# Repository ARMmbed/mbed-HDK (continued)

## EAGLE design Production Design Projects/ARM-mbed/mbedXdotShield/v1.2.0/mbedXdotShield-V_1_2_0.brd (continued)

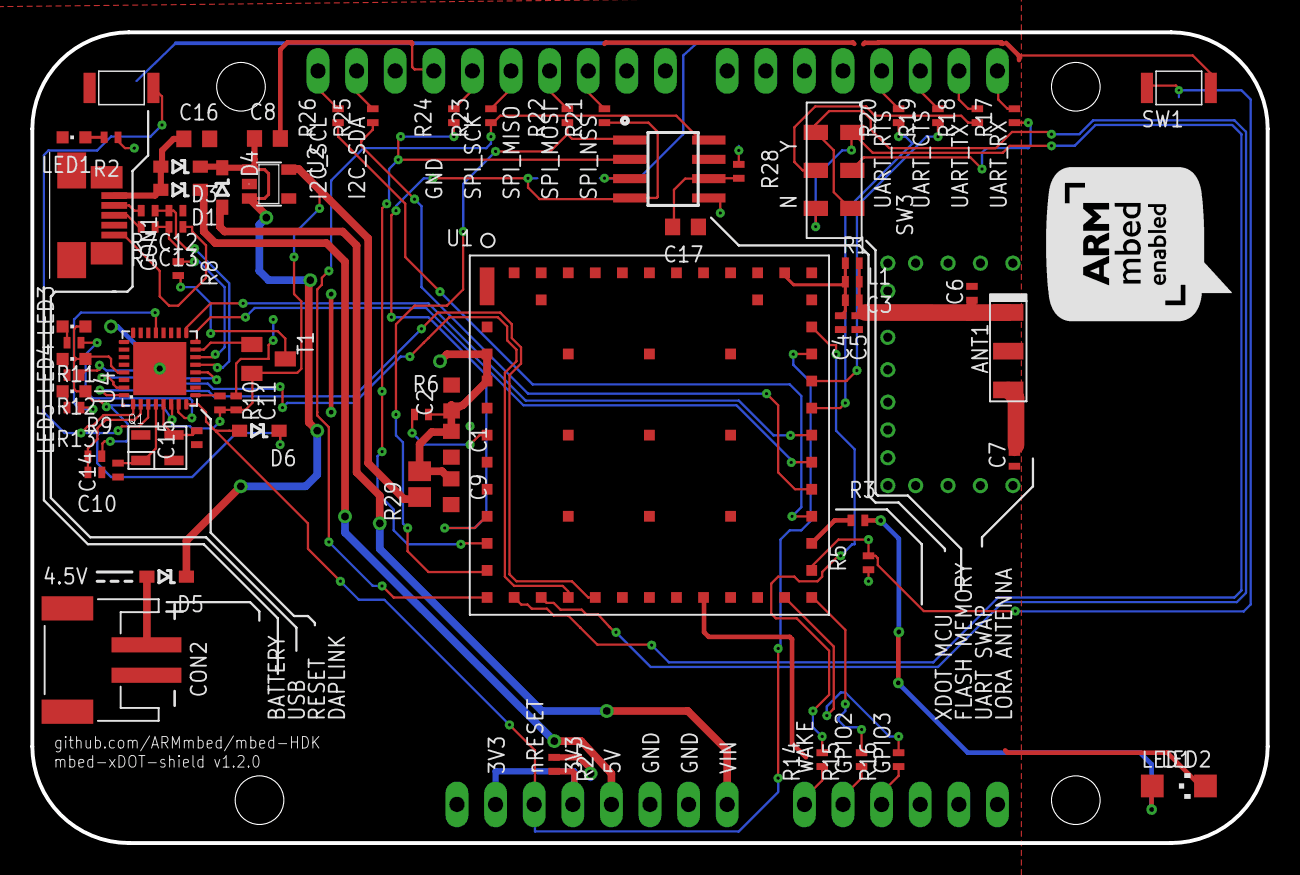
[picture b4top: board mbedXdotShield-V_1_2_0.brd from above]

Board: 2 copper layers, 81.3 x 53.3 mm, 70 parts (0 on the bottom side), 68 nets.

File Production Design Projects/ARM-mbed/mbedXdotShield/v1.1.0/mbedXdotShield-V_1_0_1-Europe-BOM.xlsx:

Qty | Value | Device | Package | Parts | Description | MF | MFN | OC-DIGIKEY | OC-MOUSER | OC-NEWARK
1 |  | IF-LPC11U35 | HVQFN33 | U4 | MCU | NXP | LPC11U35FHI33/501, | 568-9586-ND | 771-LPC11U35FHI33501 | 24W5342
3 | 0 | RESISTOR0402 | 402 | R6, R27, R28 | Resistor | Yageo | RC0402JR-070RL | 311-0.0JRCT-ND | 603-RC0402JR-070RL | 603-RC0402JR-070RL
5 | 1.5K | RESISTOR0402 | 402 | R2, R5, R8, R12, R13 | Resistor | Panasonic | ERJ-2RKF1501X | P1.50KLCT-ND | 667-ERJ-2RKF1501X | 2302656
3 | 100nF | CAPACITOR0402 | 402 | C10, C11 | Capacitor | AVX | 0402YD104KAT2A | 478-1126-1-ND | 581-0402YD104K | 1327666
3 | 100nF | CAPACITOR0603 | 603 | C2, C17 | Capacitor | AVX | 0603YC104KAT2A | 478-1239-1-ND | 581-060316C104K | 1327679
3 | 10K | RESISTOR0402 | 402 | R9, R10 | Resistor | Vishay | CRCW040210K0JNED | 541-10KJCT-ND | 71-CRCW0402J-10K-E3 | 59M6696
3 | 10uF | CAPACITOR0603 | 603 | C1, C8, C9, C16 | Capacitor | Yageo | CC0603MRX5R5BB106 | 311-1448-1-ND | 603-CC603MRX5R5BB106 | 1458902
3 | 12MHz | Q_3.2X2.5 | 3.2X.2.5 | Q1 | XTAL | TXC | 7M-12.000MAAJ-T | 887-1121-1-ND | 717-7M-12.000MAAJ-T | 84R5706
3 | 18pF | CAPACITOR0402 | 402 | C12, C13, C14, C15 | Capacitor | Murata | GRM1555C1H180JA01D | 490-5858-6-ND |  | 14T3293
14 | 220R | RESISTOR0402 | 402 | R3, R14, R15, R16, R17, R18, R19, R20, R21, R22, R23, R24, R25, R26 | Resistor | Vishay | CRCW0402220RJNED | 541-220JCT-ND | 71-CRCW0402J-220-E3 | 1514687
3 | 33R | RESISTOR0402 | 402 | R4, R7 | Resistor | Vishay | CRCW040233R0JNED | 541-33JCT-ND | 71-CRCW0402J-33-E3 | 72M6782
1 | 470R | RESISTOR0402 | 402 | R11 | Resistor | Vishay | CRCW0402470RJNED | 541-470JCT-ND | 71-CRCW0402J-470-E3 | 59M6737
3 | 47346-0001 | 47346-0001 | USB-MICRO-B-H | CON1 | USB Receptacle Horizontal Micro Type B | MOLEX | 47346-0001 |  | 538-47346-0001 | 1568026
3 | 5.6pF | CAPACITOR0402 | 402 | C4 | Capacitor | AVX | 04025U5R6BAT2A | 478-10162-1-ND | 581-04025U5R6BAT2A | 1327642RL
3 | 6.8pF | CAPACITOR0402 | 402 | C7 | Capacitor | Murata | GRM1555C1H6R8BA01D | 490-6252-1-ND | 81-GRM1555C1H6R8BA1D | 2611902
3 | 82pF | CAPACITOR0402 | 402 | C6 | Capacitor | Murata | GRM1555C1H820JA01D | 490-5879-1-ND | 81-GRM1555C1H820JA1D | 2470460
3 | 9.1pF | CAPACITOR0402 | 402 | C3 | Capacitor | Murata | GJM1555C1H9R1CB01D | 490-3112-1-ND | 81-GJM1555C1H9R1CB01 | 41M1583
3 | AT45DB321E-SHF-B | AT45DB321E-SHF-B | SO8 | U3 | Serial Flash 32 Mb 85 Mhz | Adesto Technologies | AT45DB321E-SHF-B | 1265-1072-5-ND | 988-AT45DB321E-SHF-B | 2414318
3 | BAT60A | BAT60A | SOD323 | D1, D2, D3, D4, D5 | SCHOTTKY DIODE | Infineon | BAT60AE6327HTSA1 | BAT60AE6327HTSA1CT-ND | 726-BAT60AE6327 | 85X4127
3 | BAT60J | BAT60J | SOD323 | D6 | SCHOTTKY DIODE | STMicroelectronics | BAT60JFILM | 497-3707-6-ND | 511-BAT60JFILM | 89K1218
3 | BLUE | SMD_LED0603 | CHIPLED_0603 | LED4 | LED SMD, Colour Blue | Wurth Electronics Inc | 150060BS75000 | 732-4966-1-ND | 710-150060BS75000 | 2322069
3 | BSS84 | BSS84 | SOT23-3 | T1 | MOSFET P-CHANNEL | Fairchild Semiconductor | BSS84 | BSS84CT-ND | 512-BSS84 | 58K8770
3 | GREEN | SMD_LED0603 | CHIPLED_0603 | LED5 | LED SMD, Colour Green | Wurth Electronics Inc | 150060GS75000 | 732-4971-1-ND | 710-150060GS75000 | 2322070
3 | K64F/K22F-SHIELD | K64F/K22F-SHIELD | K64F/K22F | BRD1 | Shield for K64F/K22F | SparkFun | 1568-1413-ND
3 | M620720 | M620720 | M620720 | ANT1 | Chip Antenna Ceramic ISM/M2M/IoT 868/915MHz | Ethertronics | M620720 | 939-1066-1-ND
3 | MTXDOT-EU1-A00-1 | MTXDOT-EU1-A00-1 | MTXDOT-EU1/NA1-A00-1 | U1 | Multitech xDOT LORA MODULE UFL/TRC 868MHz for Europe | Multi-Tech Systems Inc. | MTXDOT-EU1-A00-1 | 591-1292-ND
3 | RED | SMD_LED0603 | CHIPLED_0603 | LED1, LED3 | LED SMD, Colour Red | Wurth Electronics Inc | 150060RS75000 | 732-4978-1-ND | 710-150060RS75000 | 2322071
3 | S2B-PH-SM4-TB(LF)(SN) | S2B-PH-SM4-TB(LF)(SN) | S2B-PH-SM4-TB(LF)(SN) | CON2 | 2 Position 2 mm JST PH Series Pitch Surface Mount Side Entry Shrouded Header | JST | S2B-PH-SM4-TB(LF)(SN) | 455-1749-1-ND |  | 38K8067
3 | SKRKAEE010 | SKRKAEE010 | SKRKAEE010 | RESET, SW2 | MOMENTARY SWITCH PUSH VERTICAL (SPST) | ALPS | SKRKAEE010 |  | 688-SKRKAE
3 | SMD_LED1206 | SMD_LED1206 | CHIPLED_1206 | LED2 | LED SMD, Colour Blue | Wurth Electronics Inc | 150120BS75000 | 732-4989-1-ND | 710-150120BS75000 | 2322084
3 | TLV73333PDBVT | TLV73333PDBVT | SOT23-5 | U2 | LDO Fixed Regulator 3.3v, 300mA | Texas Instruments | TLV73333PDBVT | 296-38492-1-ND | 595-TLV73333PDBVT | 2455145
3 | JS202011JCQN | JS202011JCQN | JS202011JCQN | SW3 | SLIDE TOGGLE SWITCH VERTICAL (DPDT) | C&K Components | JS202011JCQN | CKN10723CT-ND | 611-JS202011JCQN

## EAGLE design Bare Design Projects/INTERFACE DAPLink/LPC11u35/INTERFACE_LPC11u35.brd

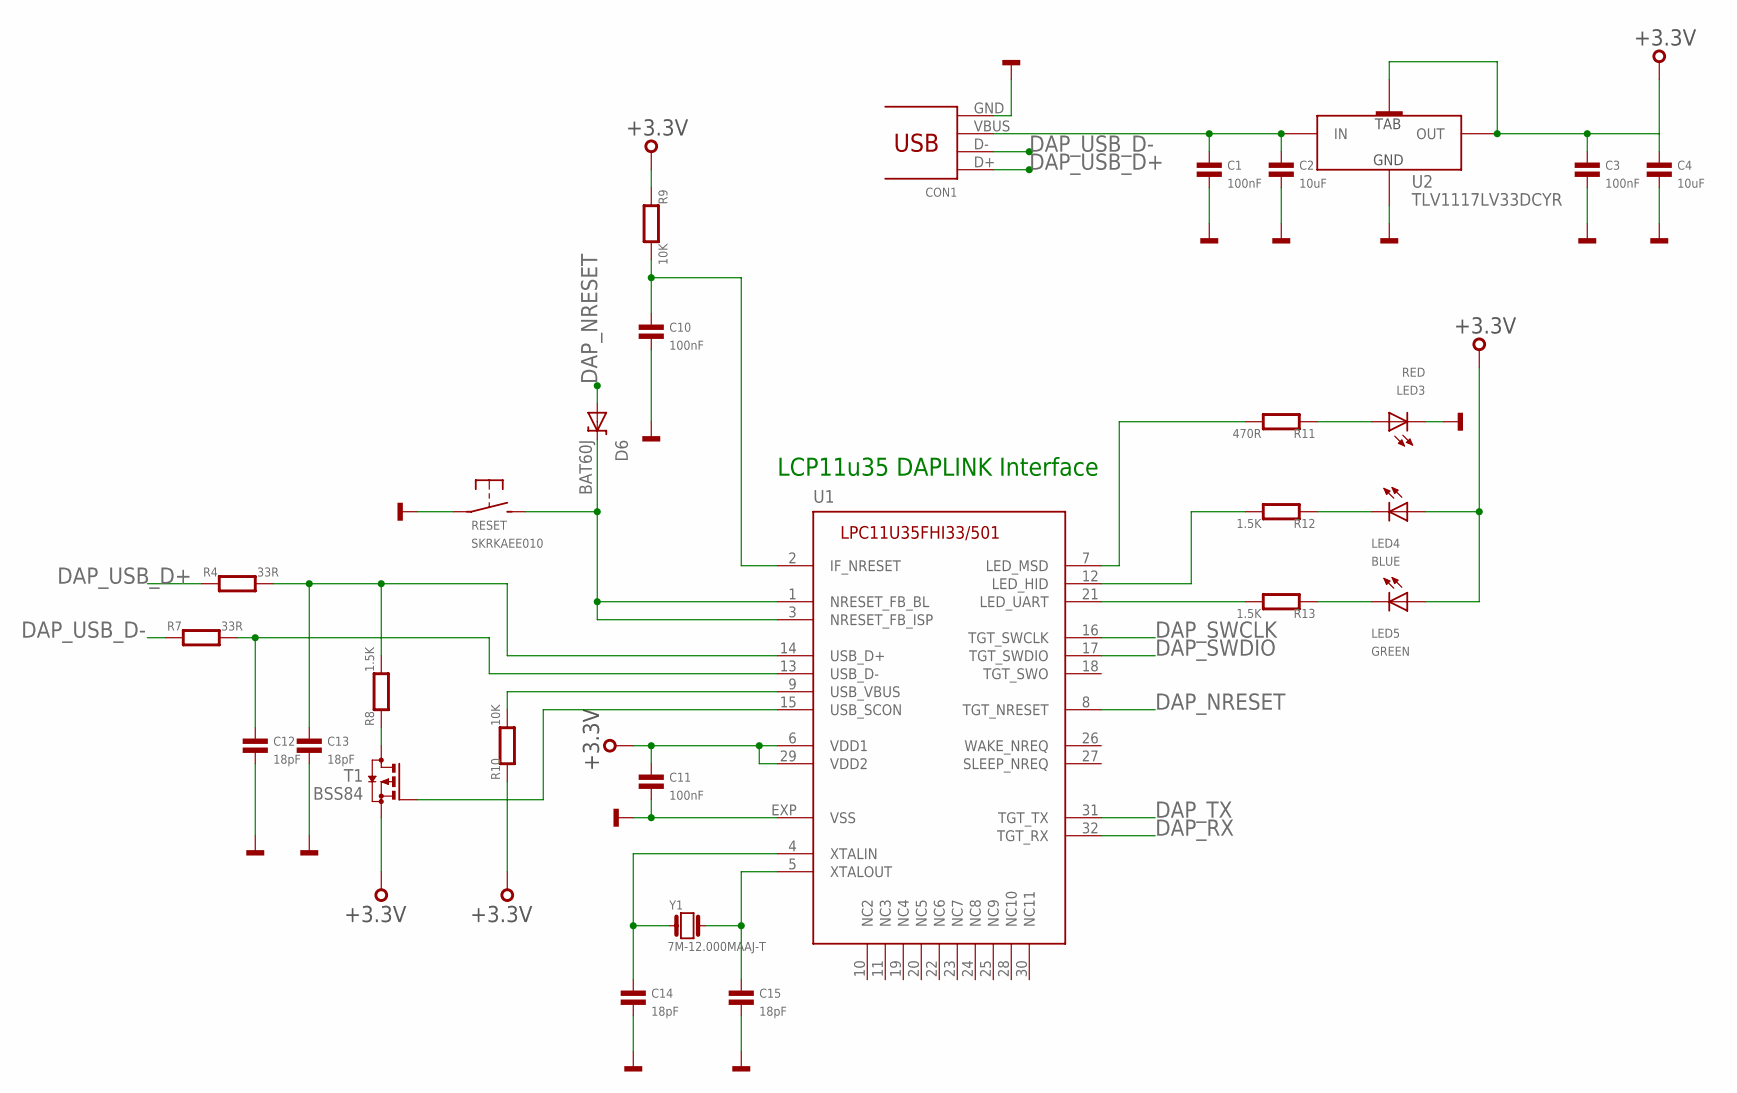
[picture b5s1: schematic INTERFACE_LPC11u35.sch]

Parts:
C1, C3, C10, C11: 100nF; 0402
C2, C4: 10uF; 0603
C12, C13, C14, C15: 18pF; 0402
CON1: 47346-0001; USB-MICRO-B-H
D6: BAT60J; SOD323
LED3: RED; CHIPLED_0603
LED4: BLUE; CHIPLED_0603
LED5: GREEN; CHIPLED_0603
R4, R7: 33R; 0402
R8, R12, R13: 1.5K; 0402
R9, R10: 10K; 0402
R11: 470R; 0402
RESET: SKRKAEE010
T1: BSS84; SOT23-3
U1: IF_LPC11U35FHI33/501; HVQFN33
U2: TLV1117LV33DCYR; SOT223
Y1: 7M-12.000MAAJ-T; 3.2X.2.5

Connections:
+3.3V: C3.1, C4.1, C11.1, LED4.A, LED5.A, R9.1, R10.1, T1.2 (S), U1.6 (VDD1), U1.29 (VDD2), U2.OUT(1) (OUT), U2.OUT(2) (TAB)
DAP_NRESET: D6.A, U1.8 (TGT_NRESET)
DAP_RX: U1.32 (TGT_RX)
DAP_SWCLK: U1.16 (TGT_SWCLK)
DAP_SWDIO: U1.17 (TGT_SWDIO)
DAP_TX: U1.31 (TGT_TX)
DAP_USB_D+: CON1.D+, R4.1
DAP_USB_D-: CON1.D-, R7.1
GND: C1.2, C2.2, C3.2, C4.2, C10.2, C11.2, C12.2, C13.2, C14.2, C15.2, CON1.GND, LED3.C, RESET.P$1, U1.EXP (VSS), U2.GND
HID: R12.2, U1.12 (LED_HID)
IF_NRESET: C10.1, R9.2, U1.2 (IF_NRESET)
ISP: D6.K, RESET.P$2 (S), U1.1 (NRESET_FB_BL), U1.3 (NRESET_FB_ISP)
MSD: R11.2, U1.7 (LED_MSD)
unnamed: C1.1, C2.1, CON1.VBUS, U2.IN
unnamed: LED3.A, R11.1
unnamed: C13.1, R4.2, R8.2, U1.14 (USB_D+)
unnamed: C12.1, R7.2, U1.13 (USB_D-)
unnamed: T1.1 (G), U1.15 (USB_SCON)
unnamed: R8.1, T1.3 (D)
unnamed: R10.2, U1.9 (USB_VBUS)
unnamed: LED4.C, R12.1
unnamed: LED5.C, R13.1
unnamed: C15.1, U1.5 (XTALOUT), Y1.P$3 (2)
unnamed: C14.1, U1.4 (XTALIN), Y1.P$1 (1)
UART: R13.2, U1.21 (LED_UART)

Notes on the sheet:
LCP11u35 DAPLINK Interface

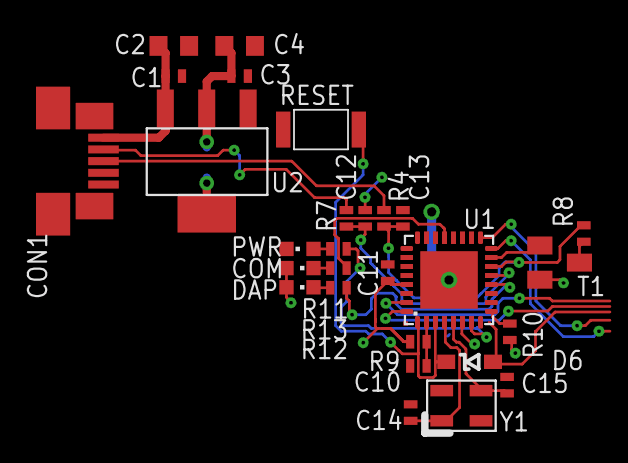
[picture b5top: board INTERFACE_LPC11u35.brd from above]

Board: 2 copper layers, 28 parts (0 on the bottom side), 21 nets.

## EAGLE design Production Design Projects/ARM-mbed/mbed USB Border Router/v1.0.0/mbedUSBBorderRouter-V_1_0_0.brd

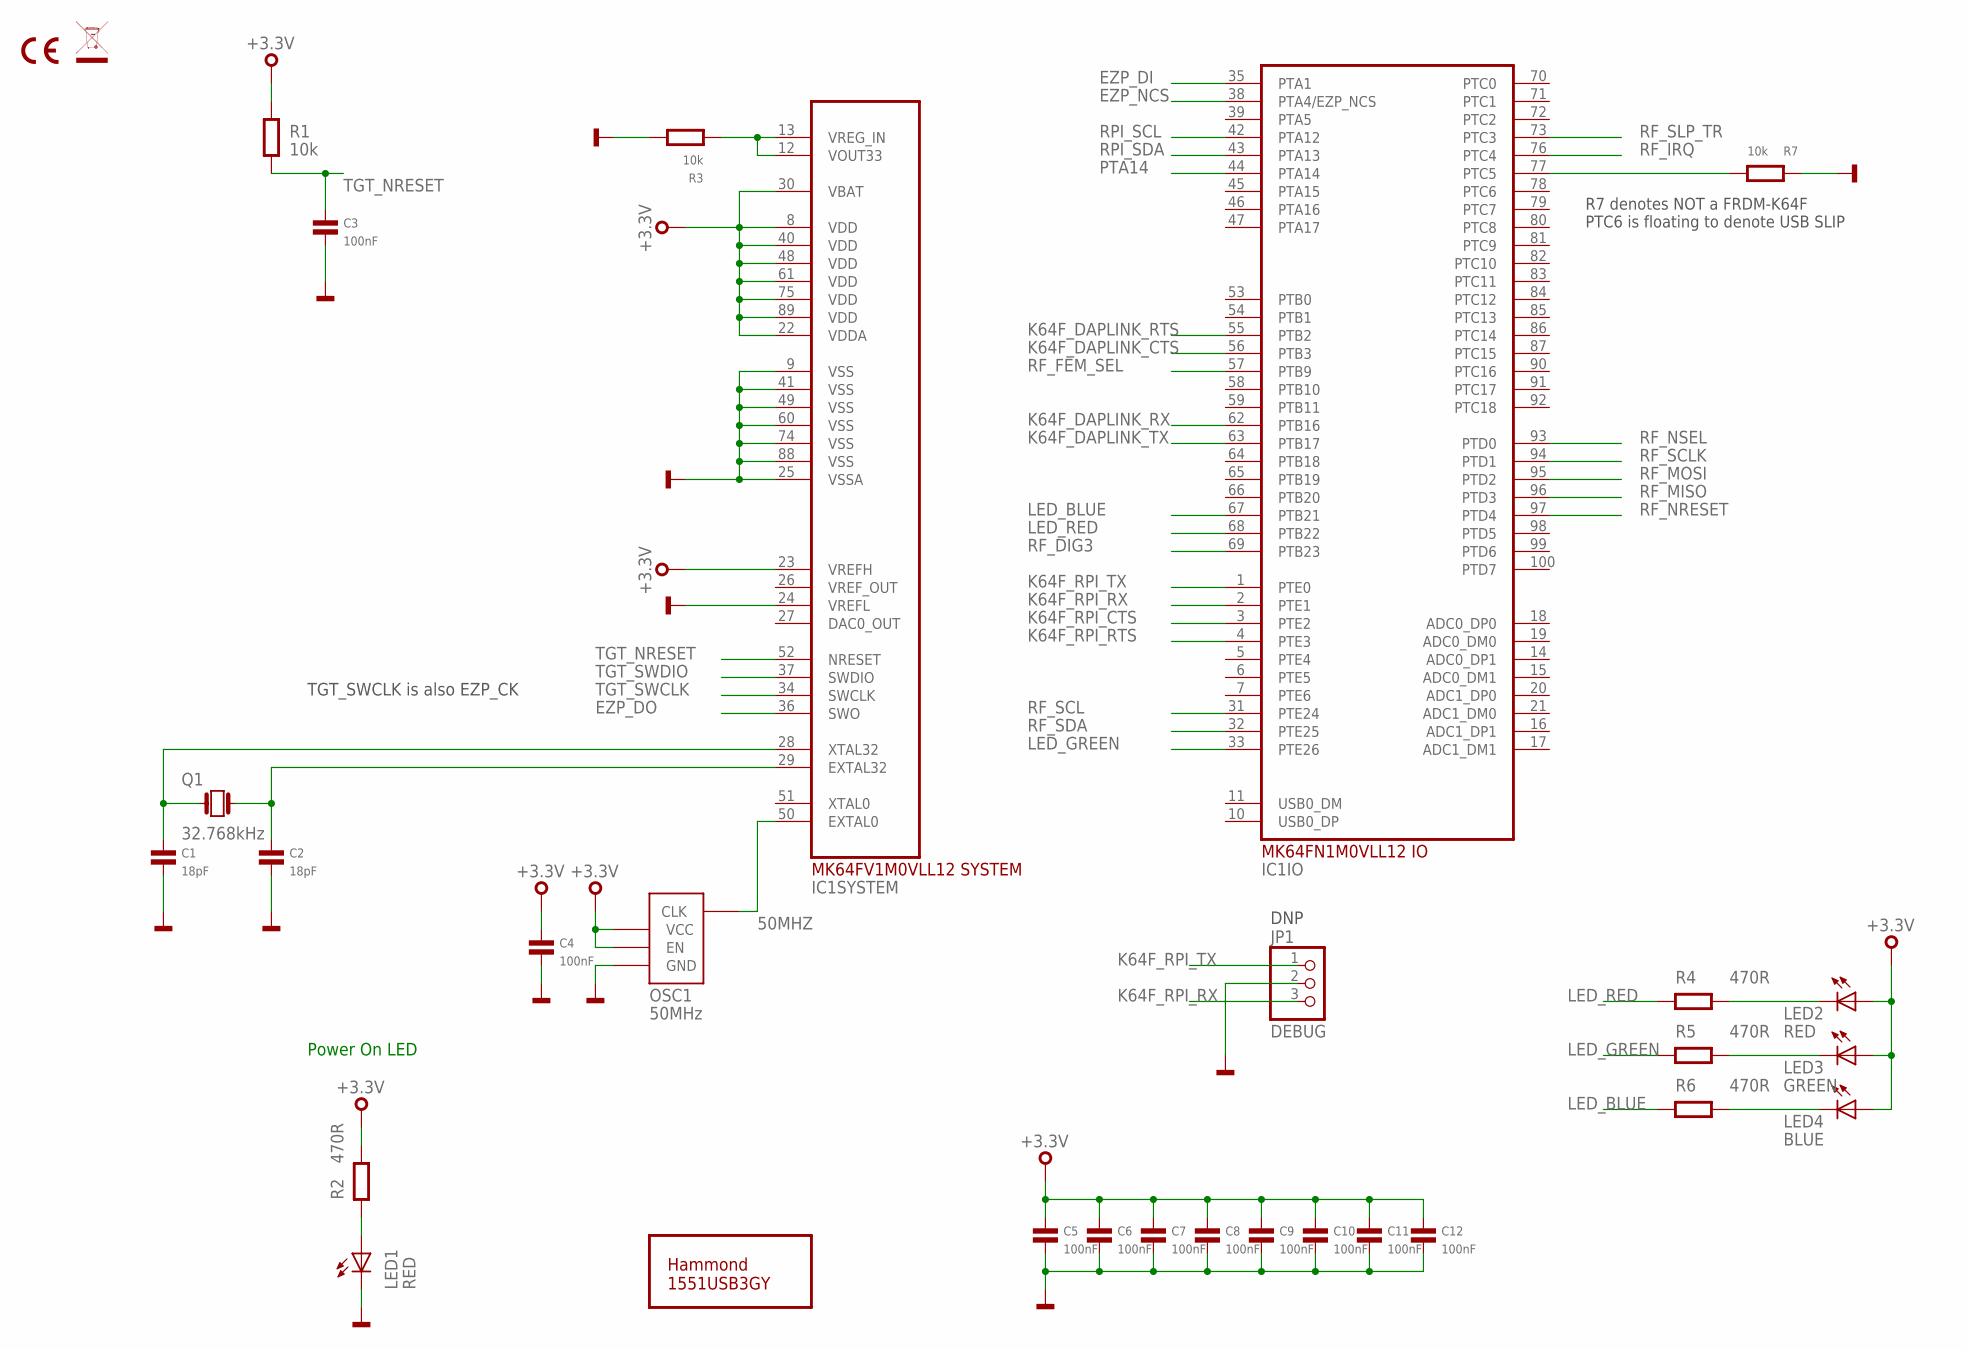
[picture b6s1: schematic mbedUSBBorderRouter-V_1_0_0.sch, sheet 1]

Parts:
BRD1: HAMMOND-1551USB3GY
C1, C2: 18pF; 0402
C3, C4, C5, C6, C7, C8, C9, C10, C11, C12: 100nF; 0402
IC1: MK64FN1M0VLL12; LQFP100
JP1: DEBUG; 1X03
LED1, LED2: RED; CHIPLED_0603
LED3: GREEN; CHIPLED_0603
LED4: BLUE; CHIPLED_0603
OSC1: 50MHz; 3.2X.2.5
Q1: 32.768kHz; FC135
R1, R3, R7: 10k; 0402
R2, R4, R5, R6: 470R; 0402
SS1: CE-MARK; CE-MARK-0.2
SS2: WEEE-MARK; WEEE-MARK-0.2

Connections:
50MHZ: IC1.50 (EXTAL0), OSC1.P$3 (CLK)
+3.3V: C4.1, C5.1, C6.1, C7.1, C8.1, C9.1, C10.1, C11.1, C12.1, IC1.8 (VDD), IC1.22 (VDDA), IC1.23 (VREFH), IC1.30 (VBAT), IC1.40 (VDD), IC1.48 (VDD), IC1.61 (VDD), IC1.75 (VDD), IC1.89 (VDD), LED2.A, LED3.A, LED4.A, OSC1.P$1 (EN), OSC1.P$4 (VCC), R1.2, R2.2; also elsewhere on the board
EZP_DI: IC1.35 (PTA1)
EZP_DO: IC1.36 (SWO)
EZP_NCS: IC1.38 (PTA4/EZP_NCS)
GND: C1.2, C2.2, C3.2, C4.2, C5.2, C6.2, C7.2, C8.2, C9.2, C10.2, C11.2, C12.2, IC1.9 (VSS), IC1.24 (VREFL), IC1.25 (VSSA), IC1.41 (VSS), IC1.49 (VSS), IC1.60 (VSS), IC1.74 (VSS), IC1.88 (VSS), JP1.2, LED1.C, OSC1.P$2 (GND), R3.2, R7.2; also elsewhere on the board
K64F_DAPLINK_CTS: IC1.56 (PTB3); also elsewhere on the board
K64F_DAPLINK_RTS: IC1.55 (PTB2); also elsewhere on the board
K64F_DAPLINK_RX: IC1.62 (PTB16); also elsewhere on the board
K64F_DAPLINK_TX: IC1.63 (PTB17); also elsewhere on the board
K64F_RPI_CTS: IC1.3 (PTE2)
K64F_RPI_RTS: IC1.4 (PTE3)
K64F_RPI_RX: IC1.2 (PTE1), JP1.3
K64F_RPI_TX: IC1.1 (PTE0), JP1.1
LED_BLUE: IC1.67 (PTB21), R6.1
LED_GREEN: IC1.33 (PTE26), R5.1
LED_RED: IC1.68 (PTB22), R4.1
unnamed: C1.1, IC1.28 (XTAL32), Q1.X1 (1)
unnamed: C2.1, IC1.29 (EXTAL32), Q1.X2 (2)
unnamed: IC1.77 (PTC5), R7.1
unnamed: IC1.12 (VOUT33), IC1.13 (VREG_IN), R3.1
unnamed: LED2.C, R4.2
unnamed: LED3.C, R5.2
unnamed: LED4.C, R6.2
unnamed: LED1.A, R2.1
PTA14: IC1.44 (PTA14)
RF_DIG3: IC1.69 (PTB23); also elsewhere on the board
RF_FEM_SEL: IC1.57 (PTB9); also elsewhere on the board
RF_IRQ: IC1.76 (PTC4); also elsewhere on the board
RF_MISO: IC1.96 (PTD3); also elsewhere on the board
RF_MOSI: IC1.95 (PTD2); also elsewhere on the board
RF_NRESET: IC1.97 (PTD4); also elsewhere on the board
RF_NSEL: IC1.93 (PTD0); also elsewhere on the board
RF_SCL: IC1.31 (PTE24); also elsewhere on the board
RF_SCLK: IC1.94 (PTD1); also elsewhere on the board
RF_SDA: IC1.32 (PTE25); also elsewhere on the board
RF_SLP_TR: IC1.73 (PTC3); also elsewhere on the board
RPI_SCL: IC1.42 (PTA12)
RPI_SDA: IC1.43 (PTA13)
TGT_NRESET: C3.1, IC1.52 (NRESET), R1.1; also elsewhere on the board
TGT_SWCLK: IC1.34 (SWCLK); also elsewhere on the board
TGT_SWDIO: IC1.37 (SWDIO); also elsewhere on the board

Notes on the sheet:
TGT_SWCLK is also EZP_CK
R7 denotes NOT a FRDM-K64F PTC6 is floating to denote USB SLIP
Power On LED
DNP

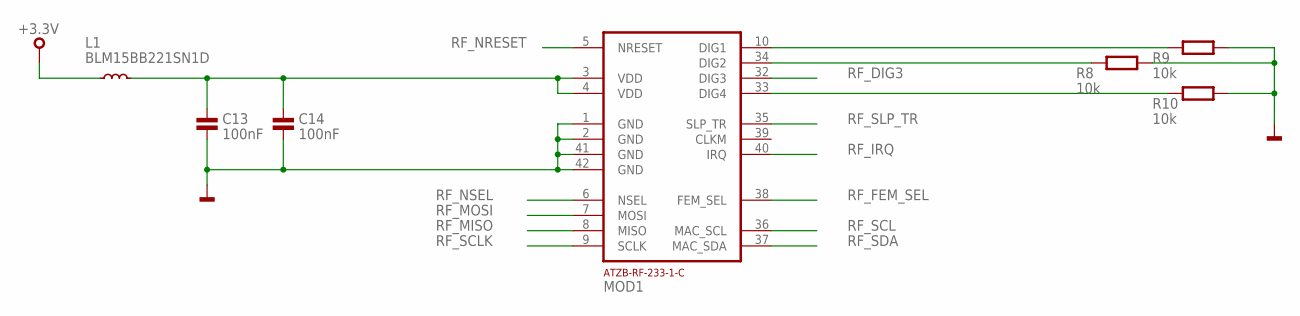
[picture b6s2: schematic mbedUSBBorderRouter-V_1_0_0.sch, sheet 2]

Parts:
C13, C14: 100nF; 0402
L1: BLM15BB221SN1D; 0402
MOD1: ATZB-RF-233-1-C
R8, R9, R10: 10k; 0402

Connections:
+3.3V: L1.1; also elsewhere on the board
GND: C13.2, C14.2, MOD1.1 (GND), MOD1.2 (GND), MOD1.41 (GND), MOD1.42 (GND), R8.2, R9.2, R10.1; also elsewhere on the board
unnamed: MOD1.10 (DIG1), R9.1
unnamed: MOD1.34 (DIG2), R8.1
unnamed: MOD1.33 (DIG4), R10.2
unnamed: C13.1, C14.1, L1.2, MOD1.3 (VDD), MOD1.4 (VDD)
RF_DIG3: MOD1.32 (DIG3); also elsewhere on the board
RF_FEM_SEL: MOD1.38 (FEM_SEL); also elsewhere on the board
RF_IRQ: MOD1.40 (IRQ); also elsewhere on the board
RF_MISO: MOD1.8 (MISO); also elsewhere on the board
RF_MOSI: MOD1.7 (MOSI); also elsewhere on the board
RF_NRESET: MOD1.5 (NRESET); also elsewhere on the board
RF_NSEL: MOD1.6 (NSEL); also elsewhere on the board
RF_SCL: MOD1.36 (MAC_SCL); also elsewhere on the board
RF_SCLK: MOD1.9 (SCLK); also elsewhere on the board
RF_SDA: MOD1.37 (MAC_SDA); also elsewhere on the board
RF_SLP_TR: MOD1.35 (SLP_TR); also elsewhere on the board

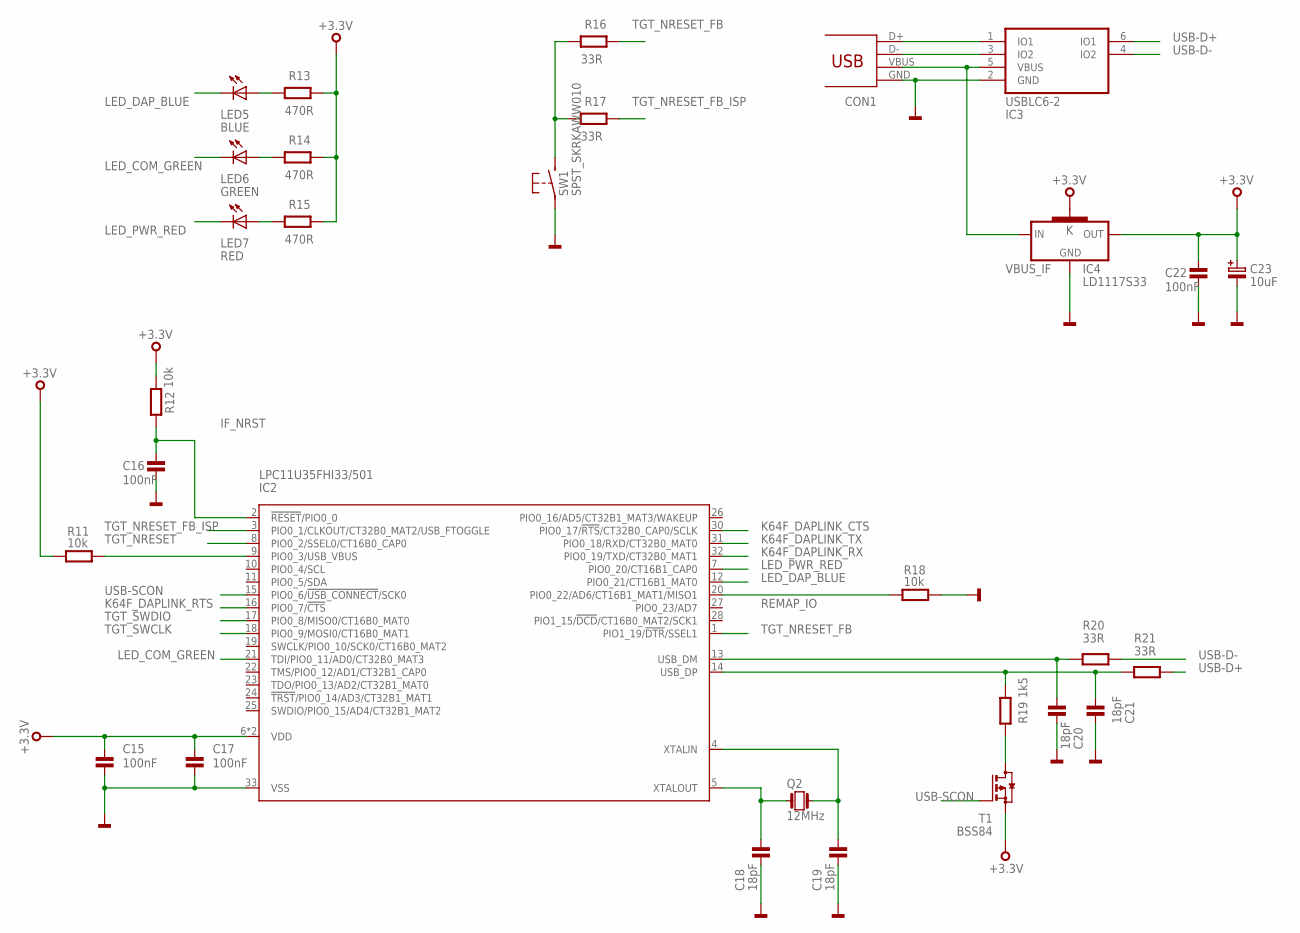
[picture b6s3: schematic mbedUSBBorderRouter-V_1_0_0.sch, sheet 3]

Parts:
C15, C16, C17, C22: 100nF; 0402
C18, C19, C20, C21: 18pF; 0402
C23: 10uF; CASE-B
CON1: USB; MOLEX-48037-2200
IC2: LPC11U35FHI33/501; SOT617-3
IC3: USBLC6-2SC6; SOT23-6L
IC4: LD1117S33; SOT223
LED5: BLUE; CHIPLED_0603
LED6: GREEN; CHIPLED_0603
LED7: RED; CHIPLED_0603
Q2: 12MHz; 3.2X.2.5
R11, R12, R18: 10k; 0402
R13, R14, R15: 470R; 0402
R16, R17, R20, R21: 33R; 0402
R19: 1k5; 0402
SW1: SPST_SKRKAWW010; SKRKAEE010
T1: BSS84; SOT23

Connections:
+3.3V: C15.1, C17.1, C22.1, C23.1, IC2.6 (VDD), IC2.29 (VDD), IC4.2 (OUT), IC4.4 (K), R11.2, R12.2, R13.1, R14.1, R15.1, T1.2 (S); also elsewhere on the board
GND: C15.2, C16.2, C17.2, C18.2, C19.2, C20.2, C21.2, C22.2, C23.2, CON1.GND, IC2.33 (VSS), IC3.2 (GND), IC4.1 (GND), R18.1, SW1.P$1; also elsewhere on the board
IF_NRST: C16.1, IC2.2 (!RESET!/PIO0_0), R12.1
K64F_DAPLINK_CTS: IC2.30 (PIO0_17/!RTS!/CT32B0_CAP0/SCLK); also elsewhere on the board
K64F_DAPLINK_RTS: IC2.16 (PIO0_7/!CTS!); also elsewhere on the board
K64F_DAPLINK_RX: IC2.32 (PIO0_19/TXD/CT32B0_MAT1); also elsewhere on the board
K64F_DAPLINK_TX: IC2.31 (PIO0_18/RXD/CT32B0_MAT0); also elsewhere on the board
LED_COM_GREEN: IC2.21 (TDI/PIO0_11/AD0/CT32B0_MAT3), LED6.C
LED_DAP_BLUE: IC2.12 (PIO0_21/CT16B1_MAT0), LED5.C
LED_PWR_RED: IC2.7 (PIO0_20/CT16B1_CAP0), LED7.C
unnamed: R16.2, R17.2, SW1.P$2 (S)
unnamed: C18.1, IC2.5 (XTALOUT), Q2.P$1 (1)
unnamed: C19.1, IC2.4 (XTALIN), Q2.P$3 (2)
unnamed: IC2.9 (PIO0_3/USB_VBUS), R11.1
unnamed: R19.1, T1.3 (D)
unnamed: LED6.A, R14.2
unnamed: LED7.A, R15.2
unnamed: LED5.A, R13.2
unnamed: CON1.D+, IC3.1 (IO1)
unnamed: CON1.D-, IC3.3 (IO2)
REMAP_IO: IC2.20 (PIO0_22/AD6/CT16B1_MAT1/MISO1), R18.2
TGT_NRESET: IC2.8 (PIO0_2/SSEL0/CT16B0_CAP0); also elsewhere on the board
TGT_NRESET_FB: IC2.1 (PIO1_19/!DTR!/SSEL1), R16.1
TGT_NRESET_FB_ISP: IC2.3 (PIO0_1/CLKOUT/CT32B0_MAT2/USB_FTOGGLE), R17.1
TGT_SWCLK: IC2.18 (PIO0_9/MOSI0/CT16B0_MAT1); also elsewhere on the board
TGT_SWDIO: IC2.17 (PIO0_8/MISO0/CT16B0_MAT0); also elsewhere on the board
USB-D+: IC3.6 (IO1), R21.1
USB-D-: IC3.4 (IO2), R20.1
USB-DM: C20.1, IC2.13 (USB_DM), R20.2
USB-DP: C21.1, IC2.14 (USB_DP), R19.2, R21.2
USB-SCON: IC2.15 (PIO0_6/!USB_CONNECT!/SCK0), T1.1 (G)
VBUS_IF: CON1.VBUS, IC3.5 (VBUS), IC4.3 (IN)

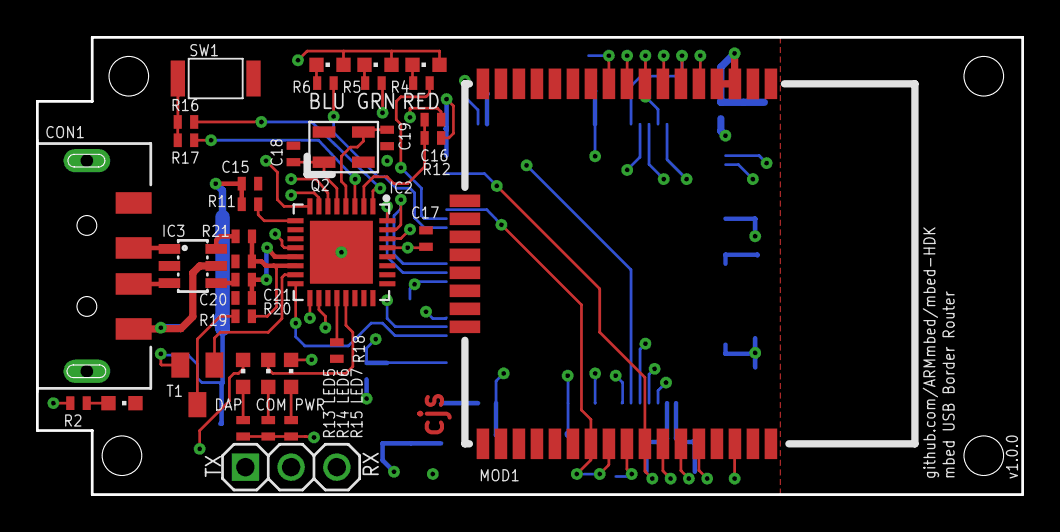
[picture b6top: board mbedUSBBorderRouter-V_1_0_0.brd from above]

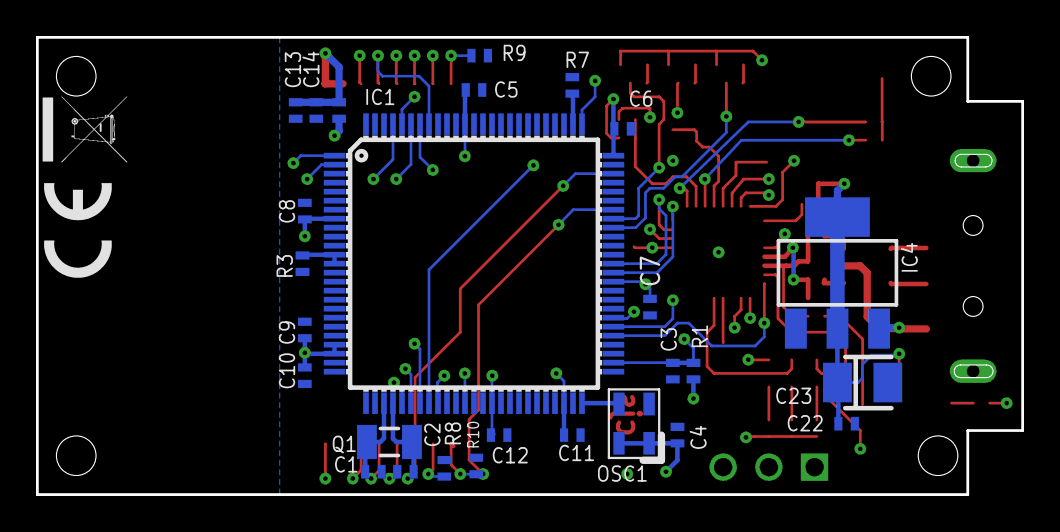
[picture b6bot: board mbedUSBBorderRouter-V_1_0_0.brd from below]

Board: 4 copper layers, 54.7 x 25.4 mm, 67 parts (27 on the bottom side), 61 nets.

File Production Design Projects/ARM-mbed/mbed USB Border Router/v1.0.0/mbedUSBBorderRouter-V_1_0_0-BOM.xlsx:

Qty | Value | Device | Package | Parts | Description | MF | MFN | OC-DIGIKEY | OC-MOUSER | OC-NEWARK
16 | 100nF | C0402 | 402 | C3, C4, C5, C6, C7, C8, C9, C10, C11, C12, C13, C14, C15, C16, C17, C22 | Capacitor | AVX | 0402YD104KAT2A | 478-1126-1-ND | 581-0402YD104K | 1327666
9 | 10k | R0402 | 402 | R1, R3, R7, R8, R9, R10, R11, R12, R18 | Resistor | Vishay | CRCW040210K0JNED | 541-10KJCT-ND | 71-CRCW0402J-10K-E3 | 59M6696
1 | 10uF | C-POL_B | CASE-B | C23 | Polarised capacitor | Kemet | T491B106K020AT | 399-8298-1-ND | 80-T491B106K020 | 57K1740
1 | 12MHz | Q_3.2X2.5 | 3.2X.2.5 | Q2 | XTAL | TXC | 7M-12.000MAAJ-T | 887-1121-1-ND | 717-7M-12.000MAAJ-T | 84R5706
6 | 18pF | C0402 | 402 | C1, C2, C18, C19, C20, C21 | Capacitor | Murata | GRM1555C1H180JA01D | 490-5858-6-ND |  | 14T3293
1 | 1k5 | R0402 | 402 | R19 | Resistor | Panasonic | ERJ-2RKF1501X | P1.50KLCT-ND | 667-ERJ-2RKF1501X | 2302656
1 | 32.768kHz | Q_FC135 | FC135 | Q1 | XTAL | Abracon | ABS07-32.768KHZ-T | 535-9542-1-ND | 815-ABS07-32.768KHZT | 2101347
4 | 33R | R0402 | 402 | R16, R17, R20, R21 | Resistor | Vishay | CRCW040233R0JNED | 541-33JCT-ND | 71-CRCW0402J-33-E3 | 72M6782
7 | 470R | R0402 | 402 | R2, R4, R5, R6, R13, R14, R15 | Resistor | Vishay | CRCW0402470RJNED | 541-470JCT-ND | 71-CRCW0402J-470-E3 | 59M6737
1 | 50MHz | OSCILLATOR3.2X2.5 | 3.2X.2.5 | OSC1 | Oscillator | Abracon | ASE-50.000MHZ-LC-T | 535-9577-1-ND |  | 2101314
1 | ATZB-RF-233-1-C | ATZB-RF-233-1-C | ATZB-RF-233-1-C | MOD1 | Atmel ZigBit Amp RF233 Module | Atmel | ATZB-RF-233-1-CR | ATZB-RF-233-1-CRCT-ND |  | 27X8560
1 | BLM15BB221SN1D | L0402 | 402 | L1 | Inductor | Murata | BLM15BB221SN1D | 490-5190-1-ND | 81-BLM15BB221SN1D | 1515769
2 | BLUE | LED0603 | CHIPLED_0603 | LED4, LED5 | SMD LED | Wurth Electronics Inc | 150060BS75000 | 732-4966-1-ND | 710-150060BS75000 | 2322069
1 | BSS84 | BSS84 | SOT23 | T1 | P-CHANNEL MOS FET | Fairchild Semiconductor | BSS84 | BSS84CT-ND | 512-BSS84 | 58K8770
2 | GREEN | LED0603 | CHIPLED_0603 | LED3, LED6 | SMD LED | Wurth Electronics Inc | 150060GS75000 | 732-4971-1-ND | 710-150060GS75000 | 2322070
1 | LD1117S33 | LD1117S33 | SOT223 | IC4 | VOLTAGE REGULATOR SMD 3,3V | STMicroelectronics | LD1117S33CTR | 497-1241-1-ND | 511-LD1117S33C | 1467779
1 | LPC11U35FHI33/501 | LPC11U35FHI33/501 | SOT617-3 | IC2 | 32-bit ARM Cortex-M0 microcontroller; up to 128 kB flash; up | NXP | LPC11U35FHI33/501 | 568-9586-ND | 771-LPC11U35FHI33501 | 2115658
1 | MK64FN1M0VLL12 | MK64FN1M0VLL12 | LQFP100 | IC1 | Kinetis K64: 120MHz Cortex-M4F MCU, 1MB Flash, 256KB SRAM, Full-Speed USB, Ethe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 | NXP | MK64FN1M0VLL12 | MK64FN1M0VLL12-ND | 841-MK64FN1M0VLL12 | 2396526
3 | RED | LED0603 | CHIPLED_0603 | LED1, LED2, LED7 | SMD LED | Wurth Electronics Inc | 150060RS75000 | 732-4978-1-ND | 710-150060RS75000 | 2322071
1 | SPST_SKRKAWW010 | SPST_SKRKAWW010 | SKRKAEE010 | SW1 | MOMENTARY SWITCH PUSH VERTICAL (SPST) | ALPS | SKRKAEE010 |  | 688-SKRKAE
1 | USB | USB | MOLEX-48037-2200 | CON1 | USB Connectors | MOLEX | 48037-2200 | WM3983CT-ND | 538-48037-2200 | 2313729
1 | USBLC6-2SC6 | USBLC6-2SC6 | SOT23-6L | IC3 | ESD USB Protection Bi-Directional | STMicroelectronics | USBLC6-2SC6 | 497-5235-1-ND | 511-USBLC6-2SC6 | 26M4748

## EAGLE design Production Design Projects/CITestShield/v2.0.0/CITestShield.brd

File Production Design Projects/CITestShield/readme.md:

## CI Test Shield

The CI Test shield is used to verify the the peripherals in a software port of mbed-os for a new board. External peripherals like PWM, Digital IO, I2C, SPI ... are all tested with the CI Test shield.

## Whats included here?

* Eagle Schematic and Board files
* PDF Schematic and Board copies
* CAM Job GERBERS for manufacture (including pick/place and drill)
* BOM (Bill of Materials)
* eBOM (An online BOM for easy purchasing!)

## Hardware

The hardware design files can be found in this repo as part of the mbed HDK and are referenced by their most up-to-date version v’x.x.x’.(If you wish to find an older project version, navigate to releases or checkout a previous commit).

## eBOM

In the HDK we provide an eBOM (Online BOM) for each production design project. This regulary updated eBOM gives the user a precompiled online list for purchasing all of the components in the design in one easy click saving you a wealth of time!

The eBOM for this project can be found [here](https://octopart.com/bom-tool/ZgvU783O)

## Software and more info

The software for tests and more info can be found in the [CI Test Shield github repository](http://www.github.com/armmbed/ci-test-shield). 

## How to get hardware

1. Buy pre-assembled board from vendor (todo)
2. Do it yourself, order [PCB from OSHPark](https://oshpark.com/shared_projects/KPFGtMVr) and parts from the BOM or eBOM.

## Revisions

- **v 2.0.0** (04/11/16)
 - Removed R13 (Removes hardware UART tests)

- **v 1.0.1** (19/09/16)
 - Initial Commit

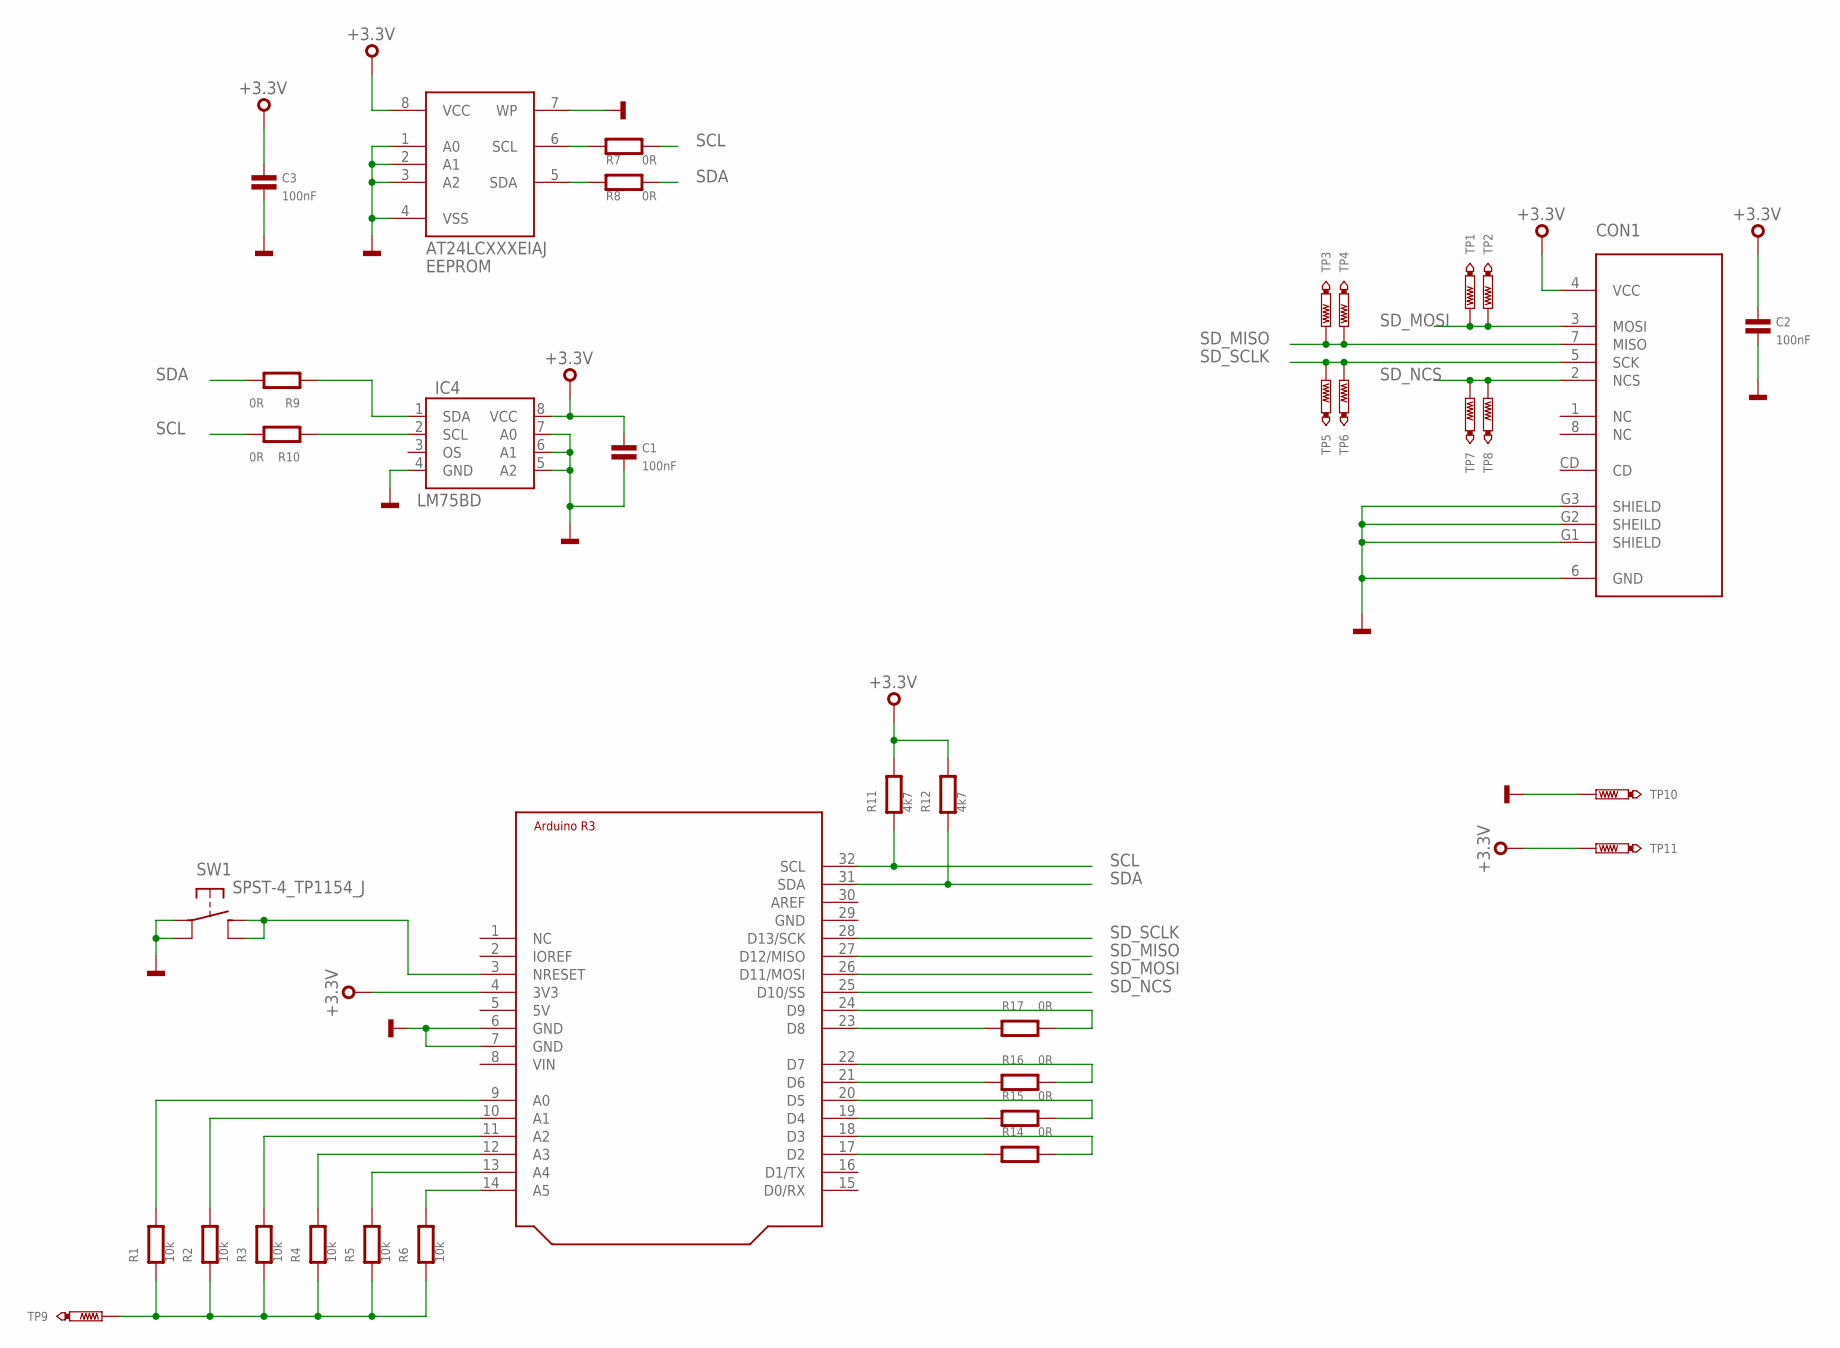
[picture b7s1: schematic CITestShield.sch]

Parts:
BRD1: ARDUINO-R3_SILK; ARDUINO-R3-SILK
C1, C2, C3: 100nF; 0603
CON1: MICRO-SD; AMPHENOL-101-00660-68-6
EEPROM: AT24LCXXXEIAJ; SO08-EIAJ
IC4: LM75BD; SO8
R1, R2, R3, R4, R5, R6: 10k; 0603
R7, R8, R9, R10, R14, R15, R16, R17: 0R; 0603
R11, R12: 4k7; 0603
SW1: SPST-4_TP1154_J; TP-1154X
TP1, TP2, TP3, TP4, TP5, TP6, TP7, TP8, TP9, TP10, TP11: TEST-POINT-50R-SMD; TP50-SMD

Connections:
+3.3V: BRD1.4 (3V3), C1.1, C2.1, C3.1, CON1.4 (VCC), EEPROM.8 (VCC), IC4.8 (VCC), R11.2, R12.2, TP11.TP
GND: BRD1.6 (GND), BRD1.7 (GND), C1.2, C2.2, C3.2, CON1.6 (GND), CON1.G1 (SHIELD), CON1.G2 (SHEILD), CON1.G3 (SHIELD), EEPROM.1 (A0), EEPROM.2 (A1), EEPROM.3 (A2), EEPROM.4 (VSS), EEPROM.7 (WP), IC4.4 (GND), IC4.5 (A2), IC4.6 (A1), IC4.7 (A0), SW1.A1, SW1.A2, TP10.TP
unnamed: R1.1, R2.1, R3.1, R4.1, R5.1, R6.1, TP9.TP
unnamed: BRD1.9 (A0), R1.2
unnamed: BRD1.10 (A1), R2.2
unnamed: BRD1.11 (A2), R3.2
unnamed: BRD1.12 (A3), R4.2
unnamed: BRD1.13 (A4), R5.2
unnamed: BRD1.14 (A5), R6.2
unnamed: BRD1.21 (D6), R16.1
unnamed: BRD1.22 (D7), R16.2
unnamed: BRD1.24 (D9), R17.2
unnamed: BRD1.23 (D8), R17.1
unnamed: BRD1.17 (D2), R14.1
unnamed: BRD1.18 (D3), R14.2
unnamed: BRD1.20 (D5), R15.2
unnamed: BRD1.19 (D4), R15.1
unnamed: BRD1.3 (NRESET), SW1.B1, SW1.B2
unnamed: IC4.2 (SCL), R10.1
unnamed: IC4.1 (SDA), R9.1
unnamed: EEPROM.6 (SCL), R7.1
unnamed: EEPROM.5 (SDA), R8.1
SCL: BRD1.32 (SCL), R7.2, R10.2, R11.1
SDA: BRD1.31 (SDA), R8.2, R9.2, R12.1
SD_MISO: BRD1.27 (D12/MISO), CON1.7 (MISO), TP3.TP, TP4.TP
SD_MOSI: BRD1.26 (D11/MOSI), CON1.3 (MOSI), TP1.TP, TP2.TP
SD_NCS: BRD1.25 (D10/SS), CON1.2 (NCS), TP7.TP, TP8.TP
SD_SCLK: BRD1.28 (D13/SCK), CON1.5 (SCK), TP5.TP, TP6.TP
